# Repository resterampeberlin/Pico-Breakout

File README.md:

# Purpose

# Credits

This open source code project is has been proudfully produced in Berlin (and other places around the globe) by

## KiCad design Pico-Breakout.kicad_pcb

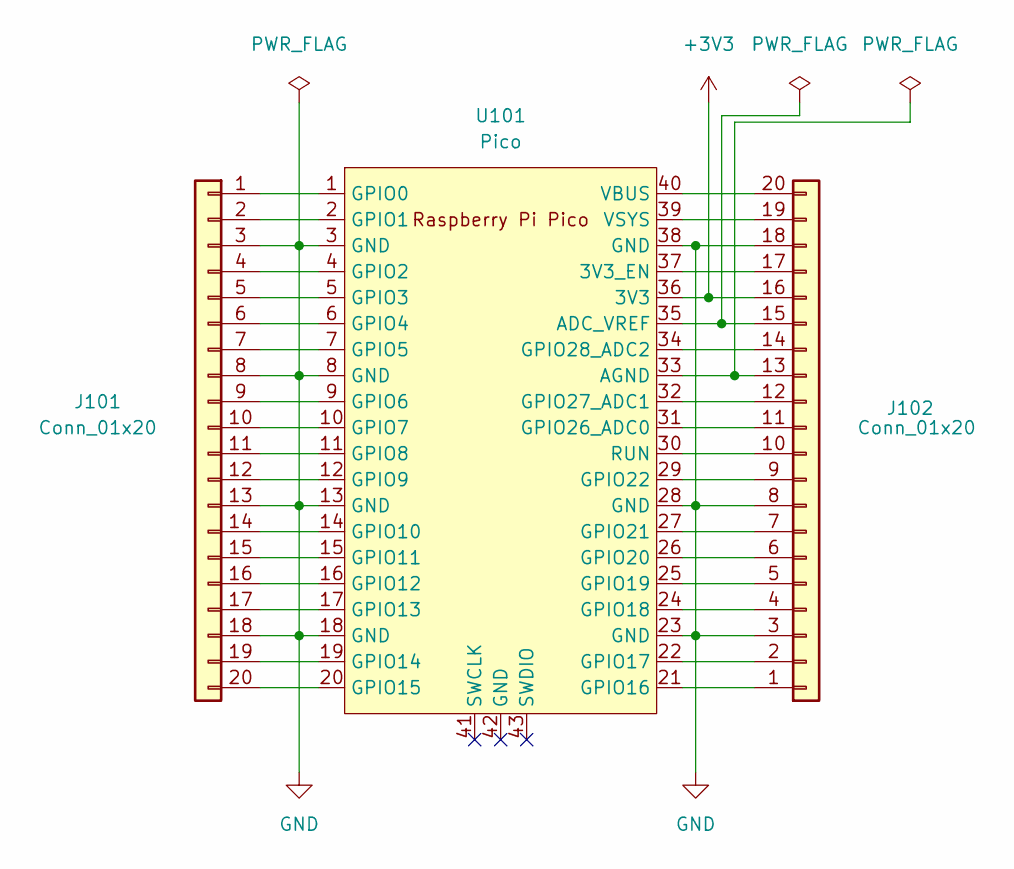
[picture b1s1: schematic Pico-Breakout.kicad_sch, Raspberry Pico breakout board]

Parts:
J101, J102: Conn_01x20; PinHeader_1x20_P2.54mm_Vertical
U101: Pico; RPi_Pico_Stacking_header_TH

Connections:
+3V3: J102.16, U101.36 (3V3)
GND: J101.3, J101.8, J101.13, J101.18, J102.3, J102.8, J102.18, U101.3 (GND), U101.8 (GND), U101.13 (GND), U101.18 (GND), U101.23 (GND), U101.28 (GND), U101.38 (GND)
unnamed: J101.1, U101.1 (GPIO0)
unnamed: J101.2, U101.2 (GPIO1)
unnamed: J101.4, U101.4 (GPIO2)
unnamed: J101.5, U101.5 (GPIO3)
unnamed: J101.6, U101.6 (GPIO4)
unnamed: J101.7, U101.7 (GPIO5)
unnamed: J101.9, U101.9 (GPIO6)
unnamed: J101.10, U101.10 (GPIO7)
unnamed: J101.11, U101.11 (GPIO8)
unnamed: J101.12, U101.12 (GPIO9)
unnamed: J101.14, U101.14 (GPIO10)
unnamed: J101.15, U101.15 (GPIO11)
unnamed: J101.16, U101.16 (GPIO12)
unnamed: J101.17, U101.17 (GPIO13)
unnamed: J101.19, U101.19 (GPIO14)
unnamed: J101.20, U101.20 (GPIO15)
unnamed: J102.1, U101.21 (GPIO16)
unnamed: J102.2, U101.22 (GPIO17)
unnamed: J102.4, U101.24 (GPIO18)
unnamed: J102.5, U101.25 (GPIO19)
unnamed: J102.6, U101.26 (GPIO20)
unnamed: J102.7, U101.27 (GPIO21)
unnamed: J102.9, U101.29 (GPIO22)
unnamed: J102.10, U101.30 (RUN)
unnamed: J102.11, U101.31 (GPIO26_ADC0)
unnamed: J102.12, U101.32 (GPIO27_ADC1)
unnamed: J102.13, U101.33 (AGND)
unnamed: J102.14, U101.34 (GPIO28_ADC2)
unnamed: J102.15, U101.35 (ADC_VREF)
unnamed: J102.17, U101.37 (3V3_EN)
unnamed: J102.19, U101.39 (VSYS)
unnamed: J102.20, U101.40 (VBUS)

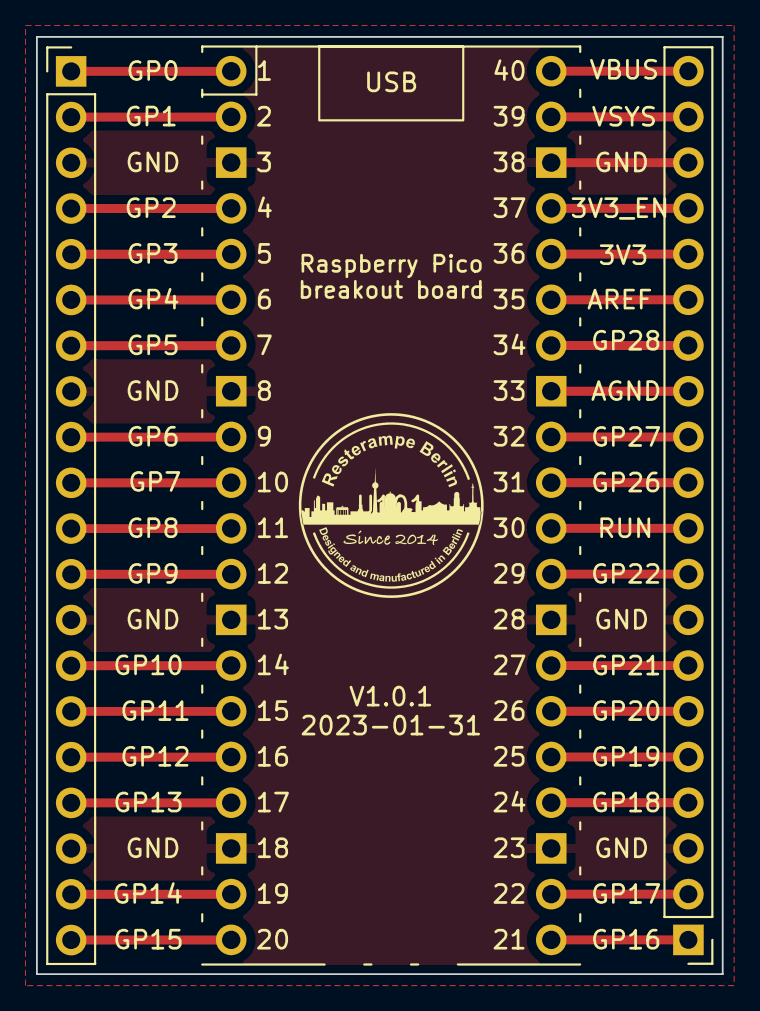
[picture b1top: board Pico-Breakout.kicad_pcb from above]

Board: 2 copper layers, 38.1 x 52.1 mm, 3 parts (0 on the bottom side), 34 nets.

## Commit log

2023-01-31 Production
2023-01-31 Documentation update, name of board on PCB
2023-02-01 Streamlined pin descriptions on PCB
2023-02-02 Added 3D stacking header
2023-02-02 Names streamlined
2023-02-12 Projet structure changed

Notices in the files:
Pico-Breakout.kicad_pcb:
https://creativecommons.org/licenses/by-nc/4.0
License CC BY-NC 4.0
